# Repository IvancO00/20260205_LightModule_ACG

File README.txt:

SETUP INSTRUCTIONS (MKR WAN 1310 as ISP)

WARNING: VOLTAGE LEVELS (3.3V vs 5V)
---------------------------------------------
Your ATmega328PB target microcontroller runs at 5V (according to the schematic).
Your Arduino MKR WAN 1310 runs at 3.3V.

DIRECTLY CONNECTING MKR PINS (3.3V) TO THE 5V BOARD CAN DAMAGE THE MKR!
The SPI lines (MISO, MOSI, SCK) must be level-shifted.

SAFE SOLUTIONS:
1. Use a bidirectional Level Shifter between MKR and Target.
2. OR: Power the target board at 3.3V (instead of 5V) by disconnecting the external 5V source and using the MKR's VCC pin (3.3V) to power the Target's VCC pin. (Note: At 16MHz the 328PB is out of spec at 3.3V, but it often works for flashing).

---------------------------------------------
STEP 1: PREPARE THE MKR WAN 1310
---------------------------------------------
1. Open the classic Arduino IDE.
2. Open the example: File > Examples > 11.ArduinoISP > ArduinoISP.
3. SCROLL THE CODE until you find: `#define RESET 10`.
   ON MKR WAN 1310, pin 10 is often used for other things or can create conflicts (MISO).
   CHANGE that line to: `#define RESET 6` (or another free digital pin).
4. ALSO MODIFY LED PINS:
   Locate `#define LED_HB 9`. Pin 9 is SCK on MKR!
   Change to `#define LED_HB 2` (or any free pin).
   Same for other LEDs if they conflict with pins 8, 9, 10.
5. Upload this sketch to your MKR WAN 1310.

---------------------------------------------
STEP 2: WIRING
---------------------------------------------
MKR WAN 1310 Pin      ->      Target J2 (ISP Connector)
-------------------------------------------------------
VCC (3.3V)            ->      VCC (Pin 3) **ONLY IF POWERING AT 3.3V**
GND                   ->      GND (Pin 5)
Pin 6 (Digital)       ->      RESET (Pin 1)  (The one defined in the sketch)
MOSI (Pin 8)          ->      MOSI (Pin 4)
MISO (Pin 10)         ->      MISO (Pin 2)
SCK  (Pin 9)          ->      SCK  (Pin 6)

*Note on MKR SPI pins: Double check pinout or silkscreen. 
On many MKR boards: MOSI=8, SCK=9, MISO=10.

---------------------------------------------
STEP 3: FLASHING WITH VS CODE
---------------------------------------------
1. Open this project in VS Code.
2. Open the `platformio.ini` file.
3. Modify the line `upload_port = COM11` inserting the real COM port of your MKR.
4. Press the "PlatformIO: Upload" icon (the right arrow in the blue bottom bar, or in the side menu).
5. To set fuses (fix speed): Run "Burn Bootloader" task.

IF ARDUINO LEONARDO IS USED AS PROGRAMMER

MARduInO LEONARDO Pin      ->      Target J2 (ISP Connector)
-------------------------------------------------------
VCC (5V)              ->      VCC 
GND                   ->      GND 
RST  (Pin 10)         ->      RESET (Pin 1)  (The one defined in the sketch)
MOSI (Pin 3)          ->      MOSI (Pin 4)
MISO (Pin 5)          ->      MISO (Pin 2)
SCK  (Pin 6)          ->      SCK  (Pin 6)

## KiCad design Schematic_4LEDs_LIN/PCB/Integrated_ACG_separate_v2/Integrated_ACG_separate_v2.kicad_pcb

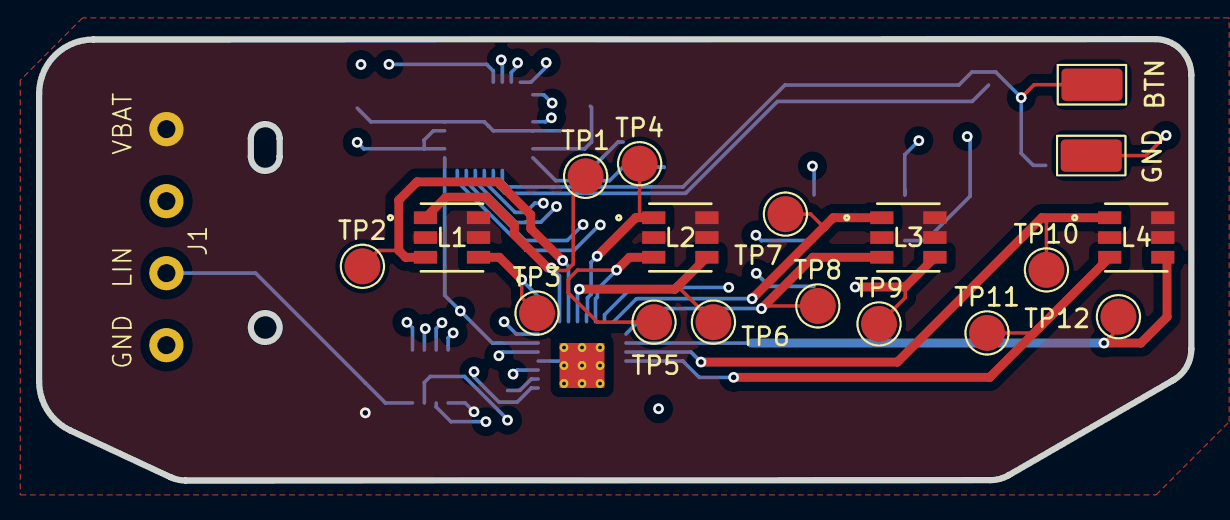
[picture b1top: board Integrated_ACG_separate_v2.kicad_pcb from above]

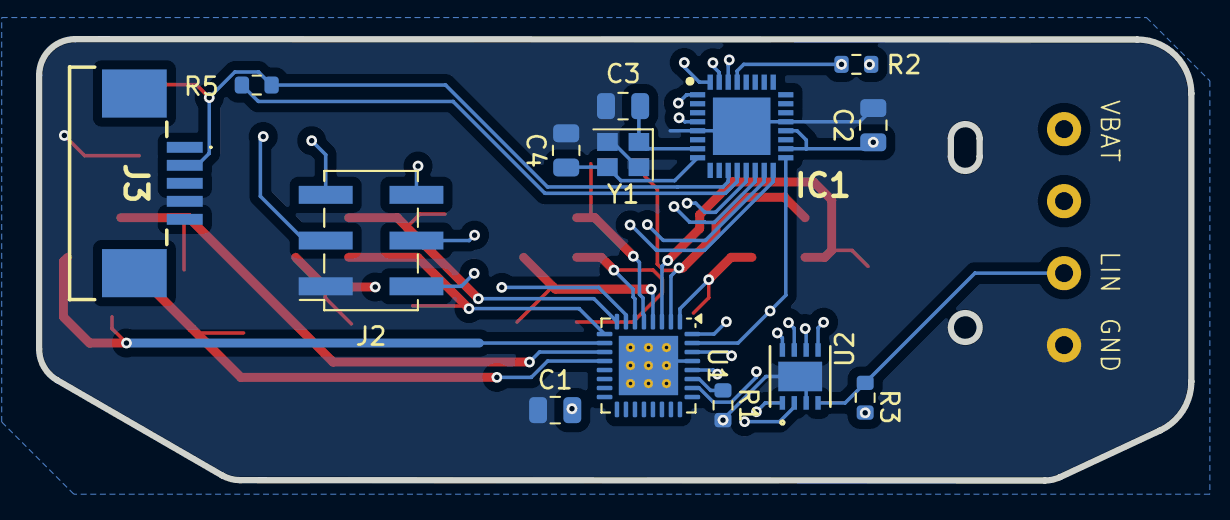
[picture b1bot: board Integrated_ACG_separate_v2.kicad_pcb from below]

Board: 4 copper layers, 64.0 x 24.5 mm, 33 parts (14 on the bottom side), 31 nets.

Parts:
BTN: TestPoint_Keystone_5015_Micro_Mini
C1: 0.1uF; C_0805_2012Metric
C2: 10 uF; C_0805_2012Metric
C3, C4: 22 pF; C_0805_2012Metric
GND: TestPoint_Keystone_5015_Micro_Mini
IC1: ATMEGA328PB-MUR; QFN50P500X500X90-33N-D
J1: Conn_01x04_Pin; MCON1.2-4
J2: FLASH; PinSocket_2x03_P2.54mm_Vertical_SMD
J3: 84952-5; 849525
L1, L2, L3, L4: RGB_LRTB; LRTB GVSG_OSR
R1: 1.6k; R_0603_1608Metric
R2, R5: 10k; R_0603_1608Metric
R3: 1k; R_0603_1608Metric
TP1, TP2, TP3, TP4, TP5, TP6, TP7, TP8, TP9, TP10, TP11, TP12: TestPoint; TestPoint_Pad_D2.0mm
U1: TLC5947RHB; QFN-32-1EP_5x5mm_P0.5mm_EP3.3x3.3mm_ThermalVias
U2: TJA1028TK/5V0/20/J; HVSON8_3X3_NXP
Y1: Crystal_GND24; Crystal_SMD_2520-4Pin_2.5x2.0mm

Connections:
+5V: C1.2, C2.1, IC1.4 (VCC), IC1.18 (AVCC), IC1.20 (AREF), J2.5, R2.1, U1.28 (VCC), U2.8 (VCC)
+12V: J1.4, L1.2 (A3), L1.5 (A2), L1.6 (A1), L2.2 (A3), L2.5 (A2), L2.6 (A1), L3.2 (A3), L3.5 (A2), L3.6 (A1), L4.2 (A3), L4.5 (A2), L4.6 (A1), R3.1, U2.1 (VBAT)
/LED_Driver/B0: L1.3 (C3), TP2.1, U1.3 (OUT2)
/LED_Driver/B1: L2.3 (C3), TP5.1, U1.6 (OUT5)
/LED_Driver/B2: L3.3 (C3), TP8.1, U1.9 (OUT8)
/LED_Driver/B3: L4.3 (C3), TP11.1, U1.12 (OUT11)
/LED_Driver/BLANK: IC1.13 ((OC1A/PTCXY)_PB1), U1.30 (BLANK)
/LED_Driver/G0: L1.1 (C1), TP1.1, U1.2 (OUT1)
/LED_Driver/G1: L2.1 (C1), TP4.1, U1.5 (OUT4)
/LED_Driver/G2: L3.1 (C1), TP7.1, U1.8 (OUT7)
/LED_Driver/G3: L4.1 (C1), TP10.1, U1.11 (OUT10)
/LED_Driver/LAT: IC1.14 ((~SS0/OC1B/PTCXY)_PB2), U1.26 (XLAT)
/LED_Driver/R0: L1.4 (C2), TP3.1, U1.1 (OUT0)
/LED_Driver/R1: L2.4 (C2), TP6.1, U1.4 (OUT3)
/LED_Driver/R2: L3.4 (C2), TP9.1, U1.7 (OUT6)
/LED_Driver/R3: L4.4 (C2), TP12.1, U1.10 (OUT9)
/uController/EN: IC1.1 ((OC2B/INT1/PTCXY)_PD3), U2.2 (EN)
/uController/LIN: J1.2, R3.2, U2.4 (LIN)
/uController/MISO: IC1.16 ((MISO0/RXD1/PTCXY)_PB4), J2.2
/uController/MOSI: IC1.15 ((MOSI0/TXD1/OC2A/PTCXY)_PB3), J2.4, U1.32 (SIN)
/uController/RST: IC1.29 (PC6_(~RESET)), J2.3, R2.2
/uController/RSTN: IC1.32 (PD2_(PTCXY/INT0/OC3B/OC4B)), U2.7 (RSTN)
/uController/RX: IC1.30 (PD0_(PTCXY/OC3A/RXD0)), U2.5 (RXD)
/uController/SCK: IC1.17 (PB5_(PTCXY/XCK1/SCK0)), J2.6, U1.31 (SCLK)
/uController/TX: IC1.31 (PD1_(PTCXY/OC4A/TXD0)), U2.6 (TXD)
/uController/XTAL1: C3.1, IC1.7 ((XTAL1/TOSC1)_PB6), Y1.1
/uController/XTAL2: C4.1, IC1.8 ((XTAL2/TOSC2)_PB7), Y1.3
GND: C1.1, C2.2, C3.2, C4.2, GND.1, IC1.5 (GND_1), IC1.21 (GND_2), IC1.33 (GND_3), J1.1, J2.1, J3.4, R1.2, U1.29 (GND), U1.33 (PowerPAD), U2.3 (GND), U2.9 (EPAD), Y1.2, Y1.4
unnamed: IC1.12 ((ICP1/CLKO/PTCXY)_PB0), R5.1
unnamed: BTN.1, IC1.11 ((PTCXY/AIN1)_PD7), J3.2, R5.2
unnamed: R1.1, U1.27 (IREF)

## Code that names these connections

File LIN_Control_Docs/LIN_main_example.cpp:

#include <Arduino.h>
#include "Adafruit_TLC5947.h"

/**
 * FIRMWARE ESEMPIO PER CONTROLLO CAMBIO LUCI VIA LIN (SERIALE 12V)
 * 
 * NOTE SUL CHIP TJA1028:
 * Per far funzionare la comunicazione, dobbiamo abilitare il transceiver.
 * U2 Pin 2 (EN)   -> ATmega PD3 (Pin 3) -> Deve essere HIGH
 * U2 Pin 7 (RSTN) -> ATmega PD2 (Pin 2) -> Deve essere HIGH
 */

// --- CONFIGURAZIONE PIN ---
#define DATA_PIN  11 
#define CLOCK_PIN 13 
#define LATCH_PIN 10 
#define BLANK_PIN 9  

// PIN ABILITAZIONE LIN TRANSCEIVER
#define LIN_EN_PIN   3
#define LIN_RST_PIN  2

#define NUM_TLC5974 1
Adafruit_TLC5947 tlc = Adafruit_TLC5947(NUM_TLC5974, CLOCK_PIN, DATA_PIN, LATCH_PIN);

// STATI DEL SISTEMA
enum LightMode {
  MODE_OFF,
  MODE_RAINBOW,
  MODE_FIXED_RGB
};

LightMode currentMode = MODE_RAINBOW; // Si parte col Rainbow
uint16_t fixedR = 0, fixedG = 0, fixedB = 0;

void setup() {
  // 1. INIZIALIZZA SERIALE (LIN)
  // Il LIN standard spesso usa 19200 o 9600 baud.
  Serial.begin(19200);

  // 2. ABILITA IL CHIP TJA1028 (Fondamentale!)
  pinMode(LIN_EN_PIN, OUTPUT);
  pinMode(LIN_RST_PIN, OUTPUT);
  digitalWrite(LIN_EN_PIN, HIGH);  // Attiva modalità Normal
  digitalWrite(LIN_RST_PIN, HIGH); // Togli Reset (Attiva il chip)

  // 3. INIZIALIZZA DRIVER LED
  pinMode(BLANK_PIN, OUTPUT);
  digitalWrite(BLANK_PIN, HIGH); 
  tlc.begin();
  digitalWrite(BLANK_PIN, LOW); // LED ON
  
  Serial.println("LIN READY. Send commands:");
  Serial.println("'R' -> Red, 'G' -> Green, 'A' -> Rainbow, 'O' -> Off");
}

// Funzione helper per settare tutti i LED insieme
void setAllLeds(uint16_t r, uint16_t g, uint16_t b) {
  for(int i=0; i<4; i++) {
    int base = i * 3;
    tlc.setPWM(base, r);
    tlc.setPWM(base+1, g);
    tlc.setPWM(base+2, b);
  }
  tlc.write();
}

// Variabili per l'animazione
uint16_t hue = 0;
unsigned long lastUpdate = 0;

void loop() {
  // --- 1. LETTURA SERIALE (LIN) ---
  if (Serial.available() > 0) {
    char cmd = Serial.read();

    // Protocollo Semplice a singolo carattere
    switch(cmd) {
      case 'R': // RED
        currentMode = MODE_FIXED_RGB;
        fixedR = 4095; fixedG = 0; fixedB = 0;
        Serial.println("CMD: Red");
        break;
      
      case 'G': // GREEN
        currentMode = MODE_FIXED_RGB;
        fixedR = 0; fixedG = 4095; fixedB = 0;
        Serial.println("CMD: Green");
        break;

      case 'B': // BLUE
        currentMode = MODE_FIXED_RGB;
        fixedR = 0; fixedG = 0; fixedB = 4095;
        Serial.println("CMD: Blue");
        break;

      case 'A': // ANIMATION (Rainbow)
        currentMode = MODE_RAINBOW;
        Serial.println("CMD: Rainbow Mode");
        break;

      case 'O': // OFF
        currentMode = MODE_OFF;
        Serial.println("CMD: Off");
        break;
        
      // Esempio comando avanzato: 'W' -> White
      case 'W': 
        currentMode = MODE_FIXED_RGB;
        fixedR = 4095; fixedG = 4095; fixedB = 4095;
        Serial.println("CMD: White");
        break;
    }
  }

  // --- 2. GESTIONE LED IN BASE ALLO STATO ---
  switch (currentMode) {
    case MODE_OFF:
      setAllLeds(0, 0, 0); // Risparmia energia ma continua ad ascoltare LIN
      break;

    case MODE_FIXED_RGB:
      // Scrive il colore salvato (in loop inutile ma sicuro)
      setAllLeds(fixedR, fixedG, fixedB);
      break;

    case MODE_RAINBOW:
      // Aggiorna l'animazione ogni 20ms senza bloccare la seriale (no delay!)
      if (millis() - lastUpdate > 20) {
        lastUpdate = millis();
        // Logica arcobaleno semplificata per brevità
        // (Copiare la funzione colorWheel completa dal vecchio main)
        hue += 50;
        if(hue > 4095) hue = 0;
        // Solo un esempio rapido: qui andrebbe la logica RGB completa
        // Per ora facciamo lampeggiare un colore rotante come placeholder
        setAllLeds(hue, 4095 - hue, (hue/2)); 
      }
      break;
  }
}

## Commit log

2026-02-05 4 RGB led control w/ arduino MKR WAN 1310 Bootloader
2026-02-05 add schematic
2026-02-05 Refreash folder
2026-02-05 Add LIN basic instruction
2026-02-05 NB! Setlight masimum power to 60%. Current problem on LED driver on pure whight if not
2026-02-06 Add new LED functions and update charging effect
2026-02-06 Edit lighting loop
2026-02-06 fix files
2026-02-10 Add main for bluetooth ESP configuration
2026-02-10 Add Bluetooth connection to th ESP
2026-02-12 fix arduino leonardo ISP programmerscript
2026-02-17 add bluetooth webb app
2026-02-17 Rename Web_App to docs for GitHub Pages
2026-02-17 add white button to index.html
2026-02-17 Add slider for RGB
2026-02-17 fix capital on Sliders
2026-02-17 Add debug window
2026-02-17 Addlogo
2026-02-17 add single ed sliders
2026-02-17 Accept all the devices
2026-02-17 debug in send command function
2026-02-17 change onimput into one charge. Connection limit
2026-02-17 Fix indexing
2026-02-17 Add 2 columns of sliders
2026-02-17 fix resetbutton
2026-02-17 add charge effect and test LEDs button
2026-03-03 Update Readme adding connections to flash the light module using the leonardo board
2026-04-27 update uploading port
